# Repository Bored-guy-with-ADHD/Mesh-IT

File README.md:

# Mesh-IT
Mesh-IT is a handheld LoRa mesh messaging device designed for offline communication. It is built around the Seeed Studio Xiao ESP32-S3 and the Wio-Sx1262 LoRa Module
The Device Has a 2.8-inch colour TFT display, a 5x7 keyboard matrix, joystick navigation, GPS support, and a custom transparent 3D-printed enclosure
# Why I made it 
I wanted to build something that feels like a real product, not something held by tape and hopes.
I made this to solve a critical problem: communication in rural areas
I chose LoRa for a reason, it has excellent range and is low power, and it's cheap, costing around 60$ for 1 unit of Mesh-IT
# Project Images
## Zine 

## PCB/schematic

## Enclosure render

# onshape links
assembly link
(https://cad.onshape.com/documents/168fda0a8f16824cccb64ee6/w/7f9acbf670b84dd77c93c7b4/e/36fa08238f3aeb1c026e0e22?configuration=default&renderMode=0&uiState=6a3eabcf2515b7f76c28e72d)

original workspace link (https://cad.onshape.com/documents/f08658297db9b835bf0cb4c0/w/964f5e8aa7a9c980c94da242/e/11eb6b47f6372a176f6b115a?renderMode=0&uiState=6a3ea8e317568eae833ef321)

STEP FILES
(https://cad.onshape.com/documents/0d6a45b3dd53ce5ed637c55e/w/97f38c8d6e16f4a215b96871/e/82edf1f08dcd1788016565fc?renderMode=0&uiState=6a39f55f4e6c75de72b5becf)
# Repository structure
This repo is divided into 3 main folders
1. Assets: Contains the zine page, PCB photo, and BOM Link
2. Hardware: contains the KiCad files, Gerber files, and enclosure files
3. Software: contains the Meshtastic source code used for the project
# BOM
|Name of the modules and components                                                                 |quantity         |Column1|Cost in INR    |Cost in USD|Vender            |payment gateway  |Link to the Components                                                                                                                                                                                                                                                                                                                                                                                                                                    |Notes                                        |
|---------------------------------------------------------------------------------------------------|-----------------|-------|---------------|-----------|------------------|-----------------|----------------------------------------------------------------------------------------------------------------------------------------------------------------------------------------------------------------------------------------------------------------------------------------------------------------------------------------------------------------------------------------------------------------------------------------------------------|---------------------------------------------|
|Seed Studio XIAO ESP32S3 & Wio-SX1262 Kit                                                          |1 unit           |       |1250Rs         |13.36 USD  |RoboCraze         |Cashfree Payments|https://robocraze.com/products/xiao-esp32s3-wio-sx1262-kit-for-meshtastic-lora                                                                                                                                                                                                                                                                                                                                                                            |                                             |
|NOVA 105050 3000mAh 3.7V Micro LiPo Battery pack with Protection                                   |1 unit           |       |448Rs          |4.79 USD   |Robu.in           |Razorpay         |https://robu.in/product/nova-105050-3000mah-3-7v-micro-lipo-battery-pack/?gad_source=1&gad_campaignid=17427802559&gbraid=0AAAAADvLFWe4R9z4PrsSQhsacUKqTIDgg&gclid=CjwKCAjwnN3OBhA8EiwAfpTYepEXeKFlBX0-ix-hSTadPWN_lD1DExHiwqJOWdFqjVTRtoTX3rnxnRoCGTcQAvD_BwE#tab-specification                                                                                                                                                                           |                                             |
|2.8-inch SPI Screen Module TFT Interface 240 x 320                                                 |1 unit           |       |502Rs          |5.36 USD   |Robu.in           |Razorpay         |https://robu.in/product/2-8-inch-spi-screen-module-tft-interface-240-x-320-without-touch/#tab-product_download_66939_tab                                                                                                                                                                                                                                                                                                                                  |                                             |
|MCP23017 IO Expander                                                                               |1 units          |       |295X2 =590Rs   |6.30 USD   |Sharvi electronics|Razorpay         |https://sharvielectronics.com/product/mcp23017-io-expander-serial-module-with-i2c-serial-interface/                                                                                                                                                                                                                                                                                                                                                       |Footprint made, cross verification to be done|
|6x6x8mm Tactile Push Button Switch                                                                 |35 units         |       |1.42X35=49.7Rs |0.53 USD   |Robu.in           |Razorpay         |https://robu.in/product/6x6x8mm-tactile-push-button-switch-pack-of-20/                                                                                                                                                                                                                                                                                                                                                                                    |                                             |
|header pins male and female                                                                        |approx 3-4 strips|       |150~           |1.62 USD   |amazon            |amazon           |https://amzn.in/d/0hcru4TC                                                                                                                                                                                                                                                                                                                                                                                                                                |                                             |
|1N4148 SMD Diodes                                                                                  |35 units         |       |2.31x35=80.85Rs|0.86 USD   |Robu.in           |Razorpay         |https://robu.in/product/1n4148-surface-mount-zener-diode-pack-of-30/                                                                                                                                                                                                                                                                                                                                                                                      |                                             |
|0.1uf 50V Electrolytic Capacitor 4�7 mm                                                            |2 units          |       |1.8x2=3.6Rs    |0.038 USD  |Sharvi electronics|Razorpay         |https://sharvielectronics.com/product/0-1uf-50v-electrolytic-capacitor-4x7-mm/?srsltid=AfmBOorWLvhkQVm3tLwfxggNZzukFgYLQLgEaaP8dhHFd3TmrdtAEbPY                                                                                                                                                                                                                                                                                                           |                                             |
|4.7k? Resistors                                                                                    |2 units          |       |1.78x4=7.12Rs  |0.076 USD  |Robu.in           |Razorpay         |https://robu.in/product/4-7k-ohm-1w-metal-film-resistor-pack-of-40/                                                                                                                                                                                                                                                                                                                                                                                       |                                             |
|5V buzzer                                                                                          |1 unit           |       |5Rs            |0.053 USD  |Robu.in           |Razorpay         |https://robu.in/product/1-month-warranty-1248/                                                                                                                                                                                                                                                                                                                                                                                                            |                                             |
|Type-C USB 5V 3.1A Boost Step-Up Power Module Lithium Battery Charging Protection Board LED Display|1 unit           |       |199Rs          |2.13 USD   |RoboticsDNA       |Razorpay         |https://roboticsdna.in/product/type-c-usb-5v-3-1a-boost-step-up-power-module-lithium-battery-charging-protection-board-led-display-usb-for-diy-charger-no-weld/?src=google&kwd=&adgroup={adgroup}&device=c&campaign={campaign}&adgroup={adgroup}&keyword=&matchtype=&gad_source=1&gad_campaignid=23684419086&gbraid=0AAAAAC-xzeHGeoXQ55OAHaQCIb7zfF5Bw&gclid=Cj0KCQjwy_fOBhC6ARIsAHKFB78in6-iXOiUay3XAbAS1s5LUVEdgtFZzN9HRiBrgJL9wrLbAssALQcaAuQGEALw_wcB\|                                             |
|K1-1504SA-03-Hroparts-SMD,10x10mm Multi-Directional Switches ROHS                                  |1 unit           |       |Rs53           |0.56 USD   |Robu.in           |Razorpay         |https://robu.in/product/k1-1504sa-03-hroparts-smd10x10mm-multi-directional-switches-rohs/?gad_campaignid=17427802703&gad_source=1&gclid=CjwKCAjwhqfPBhBWEiwAZo196rdmDN105VQjwtv__rC1z535m1vRomZS1826MCCL-oSAd58Fg23y2RoCFHkQAvD_BwE&gbraid=0AAAAADvLFWcFOfMDkpSzIEVzy6CGMtIqJ                                                                                                                                                                             |Wil need to check pinout with Multimeter     |
|868MHZ 3dbi antenna for lora                                                                       |1 Unit           |       |172Rs          |1.84 USD   |Sharvi electronics|Razorpay         |https://sharvielectronics.com/product/868mhz-lora-gateway-antenna-3dbi-gain-with-sma-male-connector/                                                                                                                                                                                                                                                                                                                                                      |                                             |
|15CM SMA Female to IPEX1 Connector Cable Thread 13mm RG1.13                                        |1 unit           |       |123Rs          |1.32USD    |Robu.in           |Razorpay         |https://robu.in/product/15cm-sma-female-to-ipex1-connector-cable-thread-13/                                                                                                                                                                                                                                                                                                                                                                               |                                             |
|10k Ohm 0.25W Metal Film Resistor                                                                  |1 unit           |       |0.35Rs         |0.37 USD   |Robu.in           |Razorpay         |https://robu.in/product/10k-ohm-0-25w-metal-film-resistor-pack-of-100/                                                                                                                                                                                                                                                                                                                                                                                    |                                             |
|L89HA GPS                                                                                          |1 unit           |       |808RS          |8.57 USD   |Robocraze         |U pay            |https://robocraze.com/products/l89ha-multi-gnss-breakout-module-for-gps-irnss-glonass-beidou-galileo-qzss-7semi?variant=47278420787424                                                                                                                                                                                                                                                                                                                    |                                             |
|MAX17048                                                                                           |1 unit           |       |339RS          |3.6 USD    |RoboCraze         |Cashfree Payments|https://robocraze.com/products/max17048-li-poly-li-ion-fuel-gauge-breakout-board-mini-7semi?variant=47279011758304                                                                                                                                                                                                                                                                                                                                        |                                             |
|4 Pin JST-XH Single Side Female Polarized Header with 300mm Wire -2.54mm pitch                     |1 unit           |       |12Rs           |0.13 USD   |Sharvi electronics|Razorpay         |https://sharvielectronics.com/product/4-pin-jst-xh-female-polarized-header-wire/                                                                                                                                                                                                                                                                                                                                                                          |                                             |
|4 Pin JST-XH Male Straight 2515 Connector 2.54mm Pitch                                             |1 unut           |       |3.25           |0.34 USD   |Sharvi electronics|Razorpay         |https://sharvielectronics.com/product/4-pin-jst-xh-male-straight-2515-connector-2-54mm-pitch/                                                                                                                                                                                                                                                                                                                                                             |                                             |
|1k Ohm 0.25W,1/4W Metal Film Resistor                                                              |1 unit           |       |0.90RS         |0.94 USD   |Robu.in           |Razorpay         |https://robu.in/product/1k-ohm-0-25w-metal-film-resistor-pack-of-100/?gad_source=1&gad_campaignid=17427802703&gbraid=0AAAAADvLFWfkXPOnTYoYm-ICU5CInBHDv&gclid=CjwKCAjwq6DQBhBVEiwA4ZD5XIj57IdVh3vHXTHFk_s1zfWJuLZ_51RYMLWJrZUY41w_fux83UwMmBoCPd0QAvD_BwE                                                                                                                                                                                                 |                                             |
|Sub-Miniature Toggle Switch (Pack of 5)                                                            |1 Unit           |       |66RS           |0.69 USD   |RoboCraze         |U pay            |https://robocraze.com/products/sub-miniature-toggle-switchpack-of-5                                                                                                                                                                                                                                                                                                                                                                                       |                                             |
|SS14 skotty diode                                                                                  |1 Unit           |       |16Rs           |0.17 USD   |Robu.in           |Razorpay         |https://robu.in/product/ss14-e3-5at-vishay-ss14-e3-5at-diode-schottky-1a-40v-do-214ac-2/                                                                                                                                                                                                                                                                                                                                                                  |                                             |
|SS8050                                                                                             |1 Unit           |       |6Rs            |0.7 USD    |Robu.in           |Razorpay         |https://robu.in/product/ss8050range200-300-jiangsu-changjing-electronics-technology-co-ltd-25v-1w-200800ma1v-1-5a-npn-to-92-3-bipolar-bjt-rohs/                                                                                                                                                                                                                                                                                                           |                                             |
|Transparent Soft Silicone Switch Cap For 6X6mm Switches                                            |35 Units         |       |160Rs          |1.69 USD   |Sharvi electronics|Razorpay         |https://sharvielectronics.com/product/transparent-soft-silicone-switch-cap-for-6x6mm-switches/                                                                                                                                                                                                                                                                                                                                                            |                                             |
|Black Rubber Cap for 10x10x9mm Five Way Switch                                                     |1 Unit           |       |18Rs           |0.20 USD   |RoboticsDNA       |Razorpay         |https://roboticsdna.in/product/black-rubber-cap-for-10x10x9mm-five-way-switch/                                                                                                                                                                                                                                                                                                                                                                            |                                             |
|PCB                                                                                                |1unit            |       |640 Rs         |6.80 USD   |JLCPCB            |N/A              |N/A                                                                                                                                                                                                                                                                                                                                                                                                                                                       |                                             |
|TOTAL                                                                                              |                 |       |5740 RS        |60.85 USD  |===               |                 |                                                                                                                                                                                                                                                                                                                                                                                                                                                          |                                             |

#   How to assemble it
1. First, take the display and align it with the cutout for the display and screw it in
2. Then put the heat inserts in the backplate
3. Then insert the switch on the right side of the enclosure
4. Then wire the switch between the battery input and the charging module, the input
5. Then glue the Charging module onto the little platform near Xiao
6. Then solder the charging module's power path to the 5V pin and GND, situated on the top left
7. and solder the bat-in
8. Then cover the battery with Kapton tape, and stick it on the back of the PCB in the designated Silkscreen area using double-sided tape(Preferred 3KG one) 
9. Then align the PCB carefully and screw everything in(The case was engineered so that the battrey wont come lose, i didnt make an enclosure to avoid squiching the battrey)
# Flashing custom firmware
To flash the firmware, you will need to open the Meshtastic web flasher (https://flasher.meshtastic.org/)
Then, in the select target section, select Seed Studio Xiao, then select your firmware file and hit flash
# Timeline
Schematic and research took me around 25 hours
and making the PCB took around 45 hours
and 3d enclosure took around 30 hours of trial and error

# Current STATUS
1. PCB design is complete
2. Enclosure is complete
3. Gerber files are included
4. Zine page is complete
5. Physical build and firmware testing are still pending
# Credits
Special thanks to the Meshtastic team for open-source software
# licence
This project is open-source and released under the MIT license

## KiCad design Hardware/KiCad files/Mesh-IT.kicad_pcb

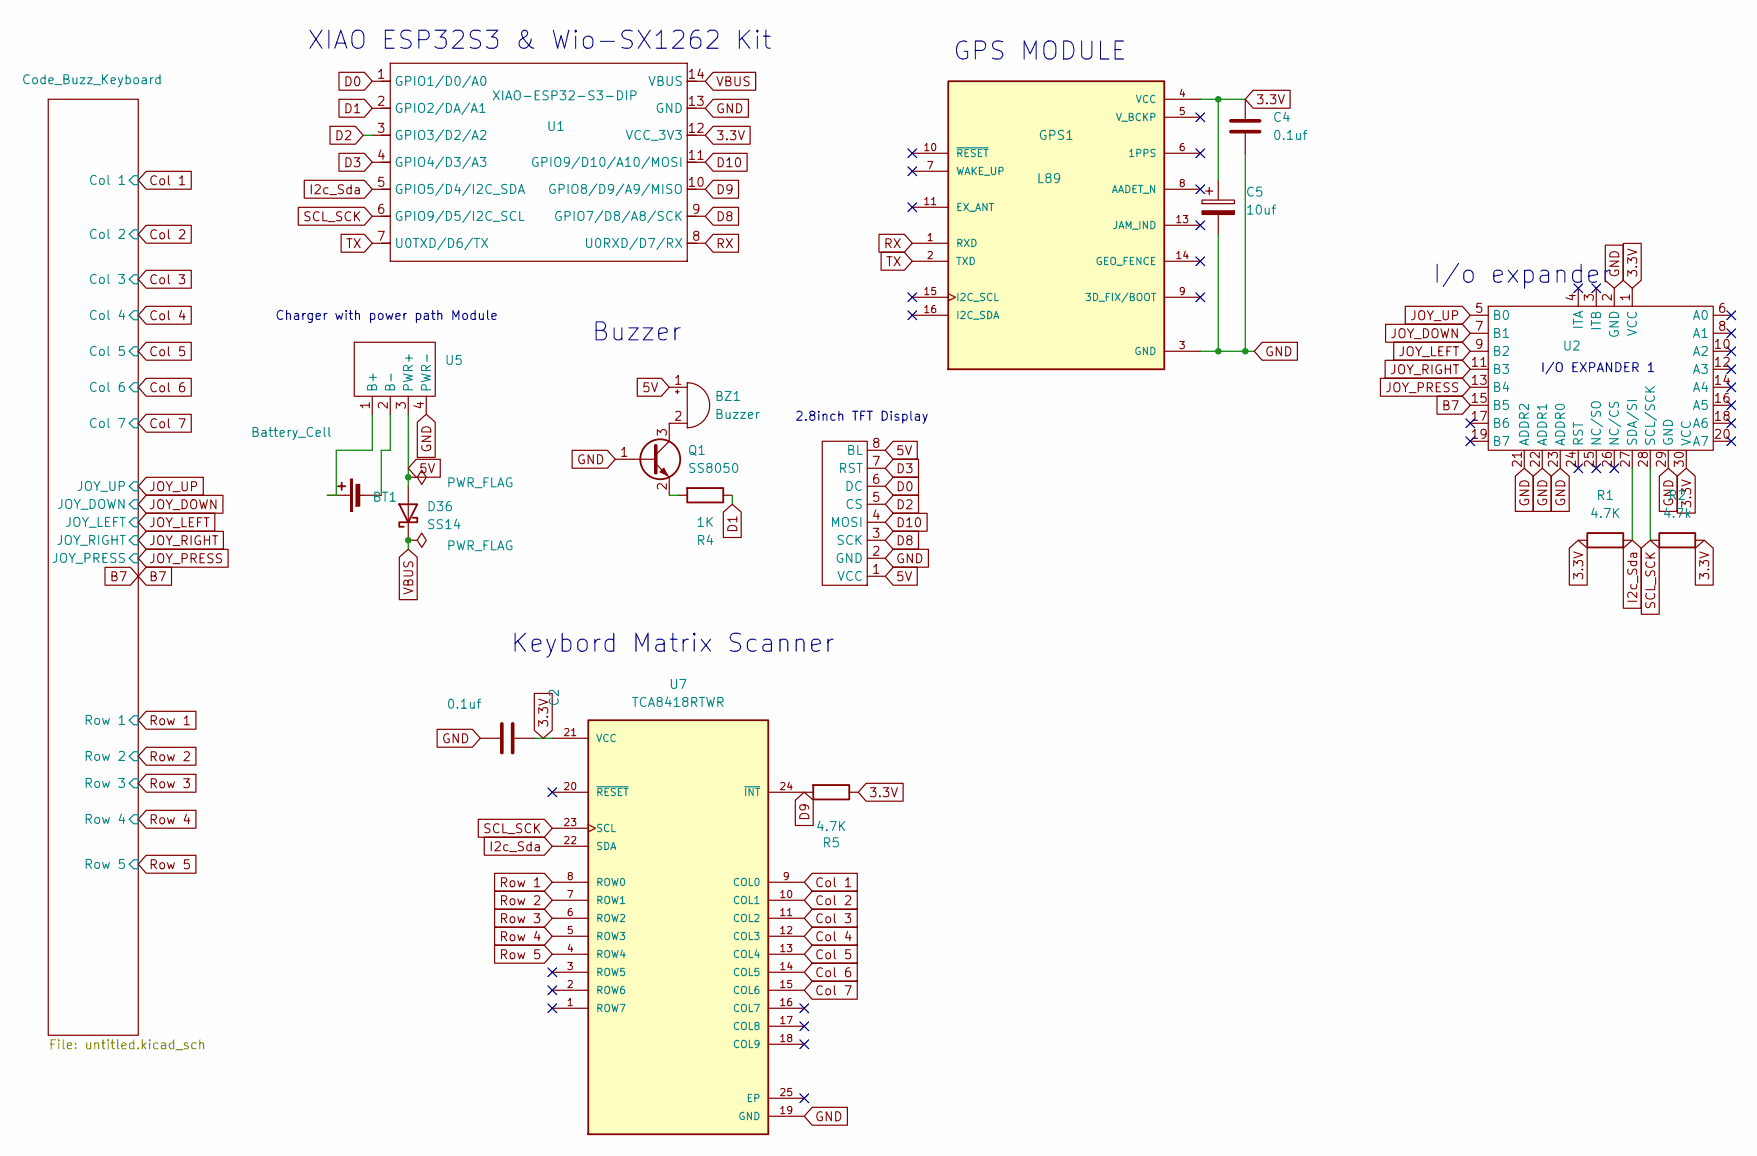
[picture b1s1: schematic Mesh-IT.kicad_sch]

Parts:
BT1: Battery_Cell; 3000Mah battrey uh
BZ1: Buzzer; Buzzer_12x9.5RM7.6
C2, C4: 0.1uf; CP_Radial_D4.0mm_P2.00mm
C5: 10uf; C_0805_2012Metric
D36: SS14; D_SMA
GPS1: L89; XCVR_L89; PARTREV 1.1
Q1: SS8050; SOT-23
R1, R5: 4.7K; R_Axial_DIN0309_L9.0mm_D3.2mm_P15.24mm_Horizontal
R2: 4.7k; R_Axial_DIN0309_L9.0mm_D3.2mm_P15.24mm_Horizontal
R4: 1K; R_Axial_DIN0204_L3.6mm_D1.6mm_P7.62mm_Horizontal
U1: XIAO-ESP32-S3-DIP; XIAO-ESP32S3-DIP
U2: io expander
U5: PinHeader_1x04_P2.54mm_Vertical
U7: TCA8418RTWR; QFN50P400X400X80-25N; PARTREV G
u3: 2.8 inch tft display

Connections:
3.3V: C2.2, C4.1, C5.1, GPS1.4 (VCC), R1.1, R2.2, R5.1, U1.12 (VCC_3V3), U2.1 (VCC), U2.30 (VCC), U7.21 (VCC)
5V: BZ1.1 (+), D36.2 (A), U5.3 (PWR+), u3.1 (VCC), u3.8 (BL)
B7: U2.15 (B5); also elsewhere on the board
Col 1: U7.9 (COL0); also elsewhere on the board
Col 2: U7.10 (COL1); also elsewhere on the board
Col 3: U7.11 (COL2); also elsewhere on the board
Col 4: U7.12 (COL3); also elsewhere on the board
Col 5: U7.13 (COL4); also elsewhere on the board
Col 6: U7.14 (COL5); also elsewhere on the board
Col 7: U7.15 (COL6); also elsewhere on the board
D0: U1.1 (GPIO1/D0/A0), u3.6 (DC)
D1: R4.1, U1.2 (GPIO2/DA/A1)
D2: U1.3 (GPIO3/D2/A2), u3.5 (CS)
D3: U1.4 (GPIO4/D3/A3), u3.7 (RST)
D8: U1.9 (GPIO7/D8/A8/SCK), u3.3 (SCK)
D9: R5.2, U1.10 (GPIO8/D9/A9/MISO), U7.24 (~INT)
D10: U1.11 (GPIO9/D10/A10/MOSI), u3.4 (MOSI)
GND: C2.1, C4.2, C5.2, GPS1.3 (GND), GPS1.12 (GND), Q1.1 (B), U1.13 (GND), U2.2 (GND), U2.21 (ADDR2), U2.22 (ADDR1), U2.23 (ADDR0), U2.29 (GND), U5.4 (PWR-), U7.19 (GND), u3.2 (GND)
I2c_Sda: R1.2, U1.5 (GPIO5/D4/I2C_SDA), U2.27 (SDA/SI), U7.22 (SDA)
JOY_DOWN: U2.7 (B1); also elsewhere on the board
JOY_LEFT: U2.9 (B2); also elsewhere on the board
JOY_PRESS: U2.13 (B4); also elsewhere on the board
JOY_RIGHT: U2.11 (B3); also elsewhere on the board
JOY_UP: U2.5 (B0); also elsewhere on the board
unnamed: BT1.1 (+), U5.1 (B+)
unnamed: BT1.2 (-), U5.2 (B-)
unnamed: BZ1.2 (-), Q1.3 (C)
unnamed: Q1.2 (E), R4.2
RX: GPS1.1 (RXD), U1.8 (U0RXD/D7/RX)
Row 1: U7.8 (ROW0); also elsewhere on the board
Row 2: U7.7 (ROW1); also elsewhere on the board
Row 3: U7.6 (ROW2); also elsewhere on the board
Row 4: U7.5 (ROW3); also elsewhere on the board
Row 5: U7.4 (ROW4); also elsewhere on the board
SCL_SCK: R2.1, U1.6 (GPIO9/D5/I2C_SCL), U2.28 (SCL/SCK), U7.23 (SCL)
TX: GPS1.2 (TXD), U1.7 (U0TXD/D6/TX)
VBUS: D36.1 (K), U1.14 (VBUS)

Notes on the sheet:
I/O EXPANDER 1
Charger with power path Module
I/o expander
XIAO ESP32S3 & Wio-SX1262 Kit
GPS MODULE
2.8inch TFT Display
Buzzer
Keybord Matrix Scanner

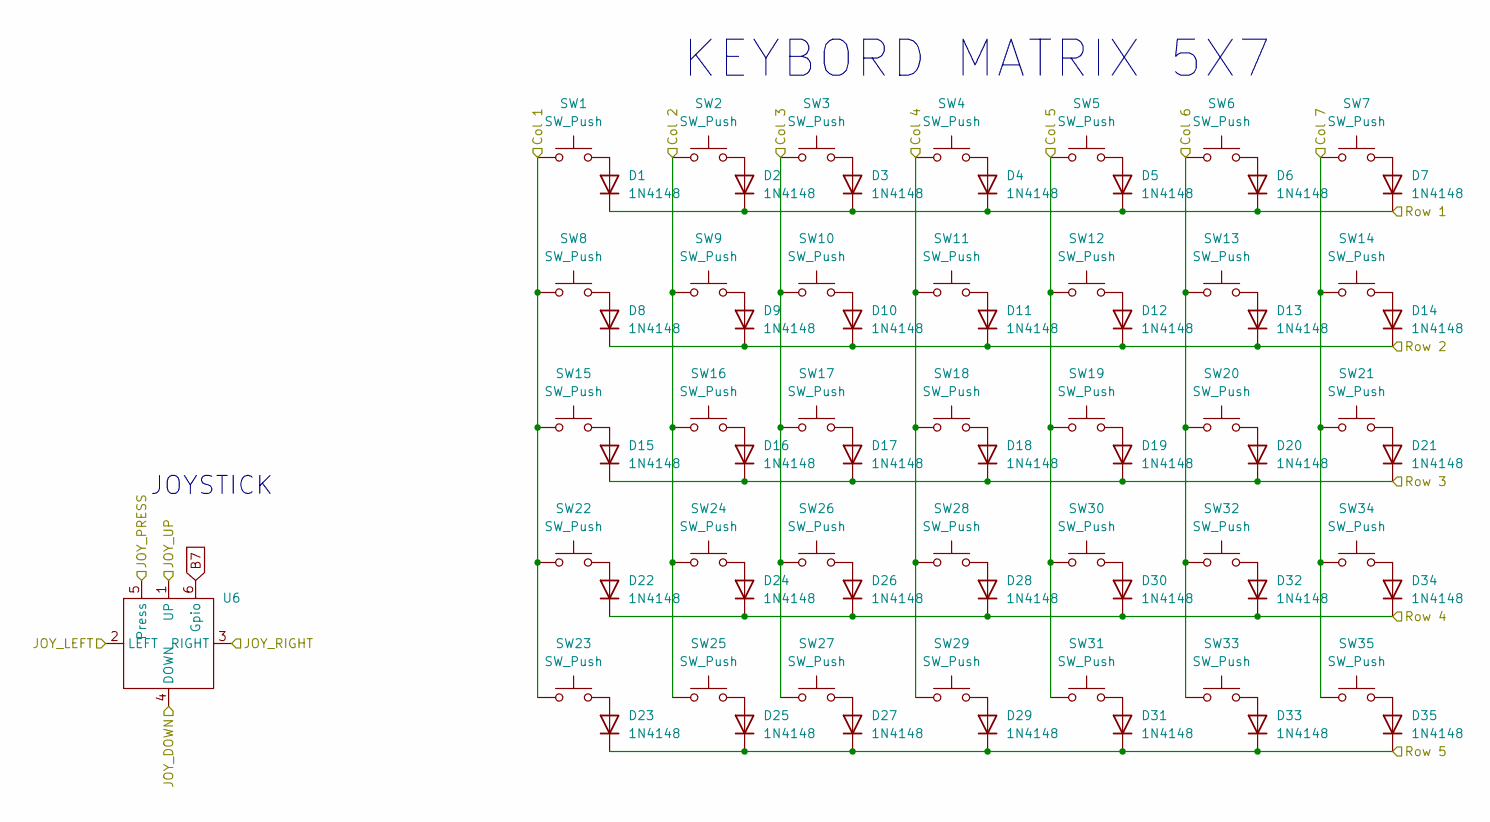
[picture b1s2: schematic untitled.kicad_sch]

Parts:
D1, D2, D3, D4, D5, D6, D7, D8, D9, D10, D11, D12, D13, D14, D15, D16, D17, D18, D19, D20, D21, D22, D23, D24, D25, D26, D27, D28, D29, D30, D31, D32, D33, D34, D35: 1N4148; D_MiniMELF
SW1, SW2, SW3, SW4, SW5, SW6, SW7, SW8, SW9, SW10, SW11, SW12, SW13, SW14, SW15, SW16, SW17, SW18, SW19, SW20, SW21, SW22, SW23, SW24, SW25, SW26, SW27, SW28, SW29, SW30, SW31, SW32, SW33, SW34, SW35: SW_Push; SW_PUSH_6mm_H8mm
U6: New Joystick

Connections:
B7: U6.6 (Gpio); also elsewhere on the board
Col 1: SW1.1, SW8.1, SW15.1, SW22.1, SW23.1; also elsewhere on the board
Col 2: SW2.1, SW9.1, SW16.1, SW24.1, SW25.1; also elsewhere on the board
Col 3: SW3.1, SW10.1, SW17.1, SW26.1, SW27.1; also elsewhere on the board
Col 4: SW4.1, SW11.1, SW18.1, SW28.1, SW29.1; also elsewhere on the board
Col 5: SW5.1, SW12.1, SW19.1, SW30.1, SW31.1; also elsewhere on the board
Col 6: SW6.1, SW13.1, SW20.1, SW32.1, SW33.1; also elsewhere on the board
Col 7: SW7.1, SW14.1, SW21.1, SW34.1, SW35.1; also elsewhere on the board
JOY_DOWN: U6.4 (DOWN); also elsewhere on the board
JOY_LEFT: U6.2 (LEFT); also elsewhere on the board
JOY_PRESS: U6.5 (Press); also elsewhere on the board
JOY_RIGHT: U6.3 (RIGHT); also elsewhere on the board
JOY_UP: U6.1 (UP); also elsewhere on the board
unnamed: D1.2 (A), SW1.2
unnamed: D2.2 (A), SW2.2
unnamed: D3.2 (A), SW3.2
unnamed: D4.2 (A), SW4.2
unnamed: D5.2 (A), SW5.2
unnamed: D6.2 (A), SW6.2
unnamed: D7.2 (A), SW7.2
unnamed: D8.2 (A), SW8.2
unnamed: D9.2 (A), SW9.2
unnamed: D10.2 (A), SW10.2
unnamed: D11.2 (A), SW11.2
unnamed: D12.2 (A), SW12.2
unnamed: D13.2 (A), SW13.2
unnamed: D14.2 (A), SW14.2
unnamed: D15.2 (A), SW15.2
unnamed: D16.2 (A), SW16.2
unnamed: D17.2 (A), SW17.2
unnamed: D18.2 (A), SW18.2
unnamed: D19.2 (A), SW19.2
unnamed: D20.2 (A), SW20.2
unnamed: D21.2 (A), SW21.2
unnamed: D22.2 (A), SW22.2
unnamed: D23.2 (A), SW23.2
unnamed: D24.2 (A), SW24.2
unnamed 51: D25.2 (A), SW25.2; also elsewhere on the board
unnamed: D26.2 (A), SW26.2
unnamed: D27.2 (A), SW27.2
unnamed: D28.2 (A), SW28.2
unnamed: D29.2 (A), SW29.2
unnamed: D30.2 (A), SW30.2
unnamed: D31.2 (A), SW31.2
unnamed: D32.2 (A), SW32.2
unnamed: D33.2 (A), SW33.2
unnamed: D34.2 (A), SW34.2
unnamed: D35.2 (A), SW35.2
Row 1: D1.1 (K), D2.1 (K), D3.1 (K), D4.1 (K), D5.1 (K), D6.1 (K), D7.1 (K); also elsewhere on the board
Row 2: D8.1 (K), D9.1 (K), D10.1 (K), D11.1 (K), D12.1 (K), D13.1 (K), D14.1 (K); also elsewhere on the board
Row 3: D15.1 (K), D16.1 (K), D17.1 (K), D18.1 (K), D19.1 (K), D20.1 (K), D21.1 (K); also elsewhere on the board
Row 4: D22.1 (K), D24.1 (K), D26.1 (K), D28.1 (K), D30.1 (K), D32.1 (K), D34.1 (K); also elsewhere on the board
Row 5: D23.1 (K), D25.1 (K), D27.1 (K), D29.1 (K), D31.1 (K), D33.1 (K), D35.1 (K); also elsewhere on the board

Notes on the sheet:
JOYSTICK
KEYBORD MATRIX 5X7

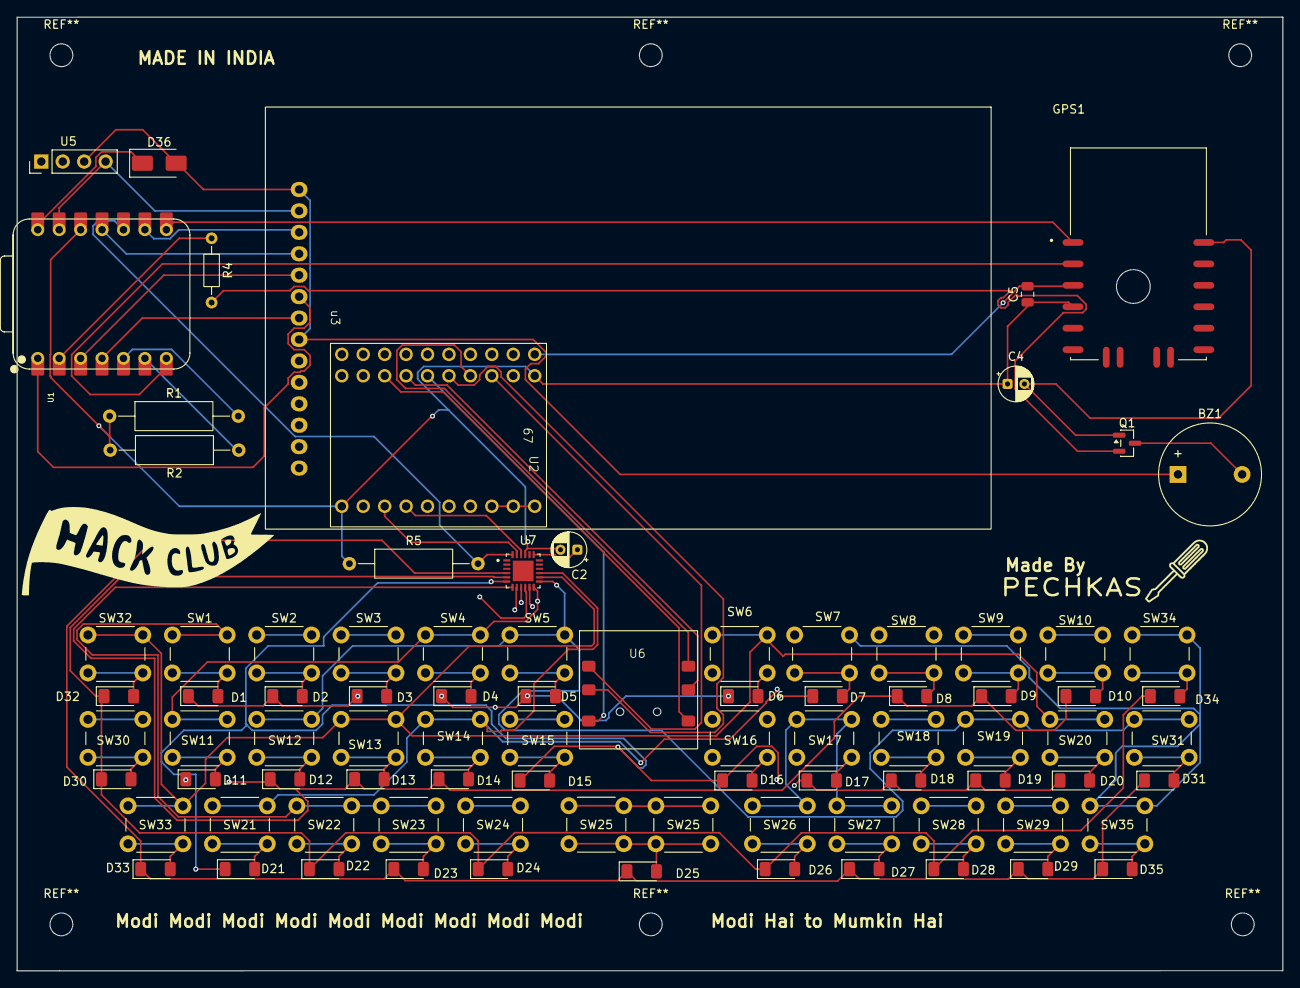
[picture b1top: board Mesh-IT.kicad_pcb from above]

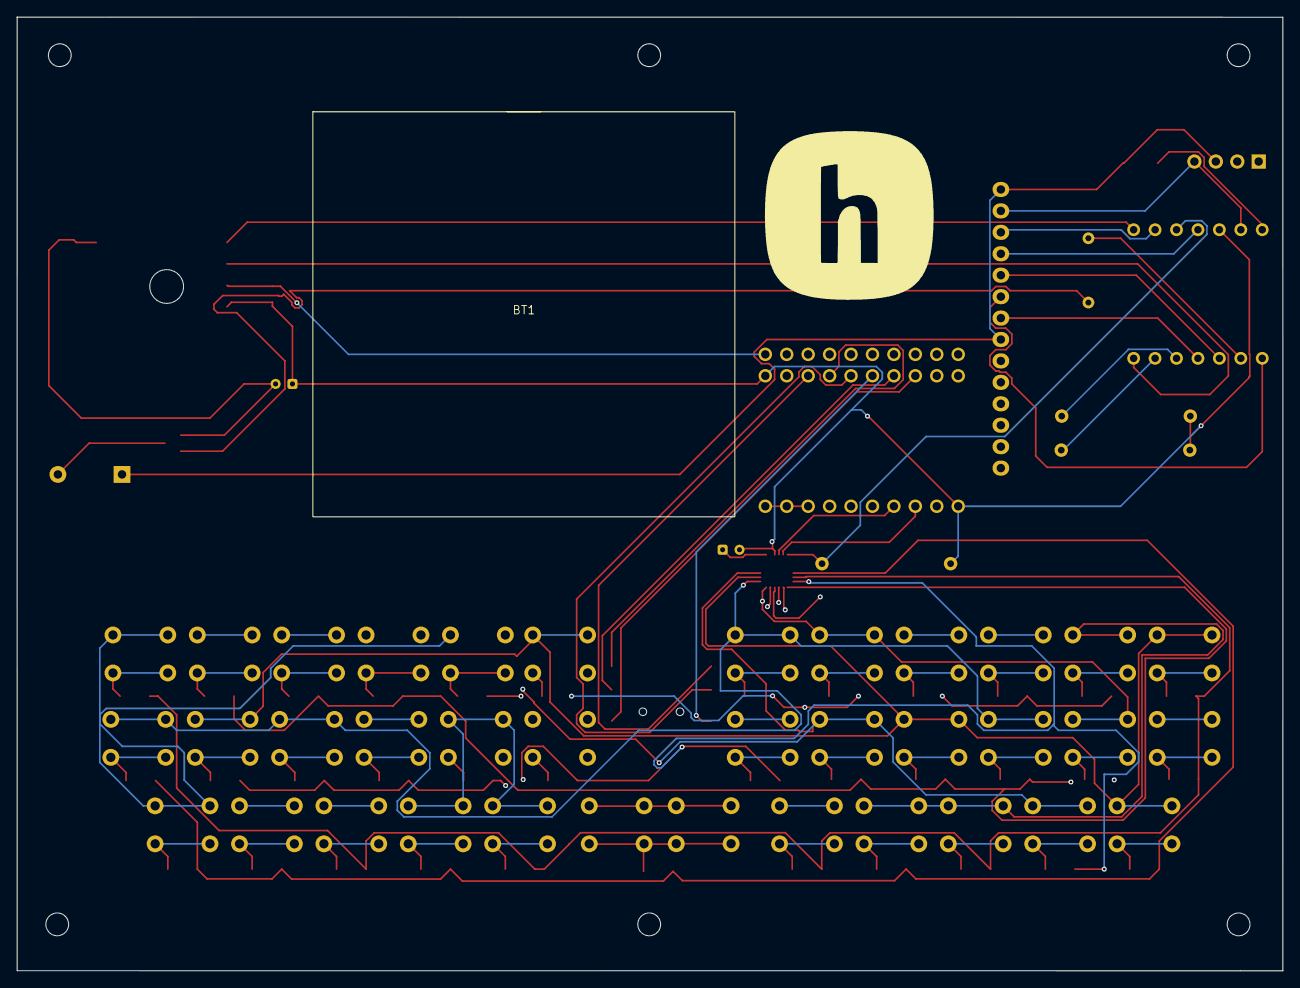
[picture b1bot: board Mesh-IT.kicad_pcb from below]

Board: 4 copper layers, 150.0 x 113.0 mm, 91 parts (2 on the bottom side), 70 nets.

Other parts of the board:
., .#2: LOGO
SW25#2: SW_Push; SW_PUSH_6mm_H8mm

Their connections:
Col 2: SW25#2.1; also elsewhere on the board
unnamed 51: SW25#2.2; also elsewhere on the board

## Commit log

2026-05-21 Update README with LoRa Module and keyboard details
2026-06-12 Rename project from CodeBuzz-Relay to Mesh-IT
    Updated project name and description for clarity.
2026-06-20 Add files via upload
    GERBERS
2026-06-20 Revise README with comprehensive project details
    Expanded the README to include detailed features, repository information, enclosure design, build instructions, credits, and licensing.
2026-06-20 Update README.md with images and additional details
    Added images to enhance the README content.
2026-06-20 Revise README.md for Mesh-IT project details
    Updated README.md to provide a comprehensive overview of the Mesh-IT project, including features, assembly instructions, and credits.
2026-06-20 organize repo files
    Organize repo files
2026-06-20 Enhance README with project details and instructions
    Expanded README.md to provide detailed project information, images, assembly instructions, and current status.
2026-06-20 Add BOM section with components and costs
    Added a Bill of Materials (BOM) section with detailed components and their costs.
2026-06-20 Replacing files with new version
2026-06-20 Rename codeBuzz copy.kicad_pcb to Mesh-IT.kicad_pcb
2026-06-20 Add Mesh-IT.kicad_pro file
2026-06-20 something changed
2026-06-20 test
2026-06-20 Uploading final files
2026-06-20 hardwork
2026-06-20 Refactor variant.h for improved readability
    Updated comments and pin definitions for clarity and organization.
2026-06-22 uhhh
    test
2026-06-23 Re uploading fixed files
2026-06-23 Fix typos and improve instructions in README
    Updated README.md for clarity and corrected typos.
2026-06-23 Renaming
2026-06-23 fixing double onshape url
2026-06-23 changing the onshape .url file to .txt file
2026-06-23 Rename fallout_zine.png.png to fallout_zine
2026-06-23 Add fallout_zine.png asset
2026-06-23 Rename fallout_zine.pdf.pdf to fallout_zine.pdf
2026-06-23 Rename fallout_zine.pdf to fallout_zine
2026-06-23 Re-uploading ccorruptedfiles
2026-06-23 curropted again due to name change
2026-06-23 Update README with new images for Zine and PCB
    Added a new image to the Zine section and updated the PCB section with an image.
2026-06-23 Changes based on review
2026-06-23 Add Onshape document link
2026-06-26 Revise BOM formatting and add assembly instructions
    Updated the BOM section with corrected formatting, quantities, and links for components. Added a section on assembly instructions.
2026-06-26 Add onshape_link_step file
2026-06-26 Add original Onshape link
2026-06-26 changer based on reviewers feedback
2026-06-26 Add Onshape assembly link for Mesh-IT enclosure
2026-06-26 Update PCB section with schematic images
2026-06-26 done last commiit
2026-06-26 changed master file name
2026-06-26 Update README with new images and links
    Added additional images and onshape links to the README.
2026-06-26 Update README with Onshape links
    Added Onshape links for assembly, original workspace, and STEP files.
2026-06-26 Add Onshape links to README
    formatting

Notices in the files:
README.md:
licence:
This project is open-source and released under the MIT license
